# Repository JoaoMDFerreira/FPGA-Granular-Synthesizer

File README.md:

# FPGA Implementation of a Real-time Synthetic-Based Granular Synthesizer
This repo contains the source code backup of the thesis. The topic of the thesis is "FPGA Implementation of a Real-time Synthetic-Based Granular Synthesizer".
A diagram of the implementation is shown below.

The final binary is given as BOOT.bin.

## VHDL Source Files
The VHDL project was not backed up, only its source files. These files are available in the vhdl_src folder.

## PCB Files
The KiCad files for a breakout board developed for the Z-turn board V2 are given in the Breakout folder.

## MATLAB Source Files
MATLAB source files are given in the matlab_src.

## Extras
Some extra files are contained in the misc_src folder. Some of these are scripts used to generate plots for the thesis, there are some exploratory scripts towards pitch_shifting that was future work for the thesis and finally there is a C script used to generate code for the MIDI_LUT.

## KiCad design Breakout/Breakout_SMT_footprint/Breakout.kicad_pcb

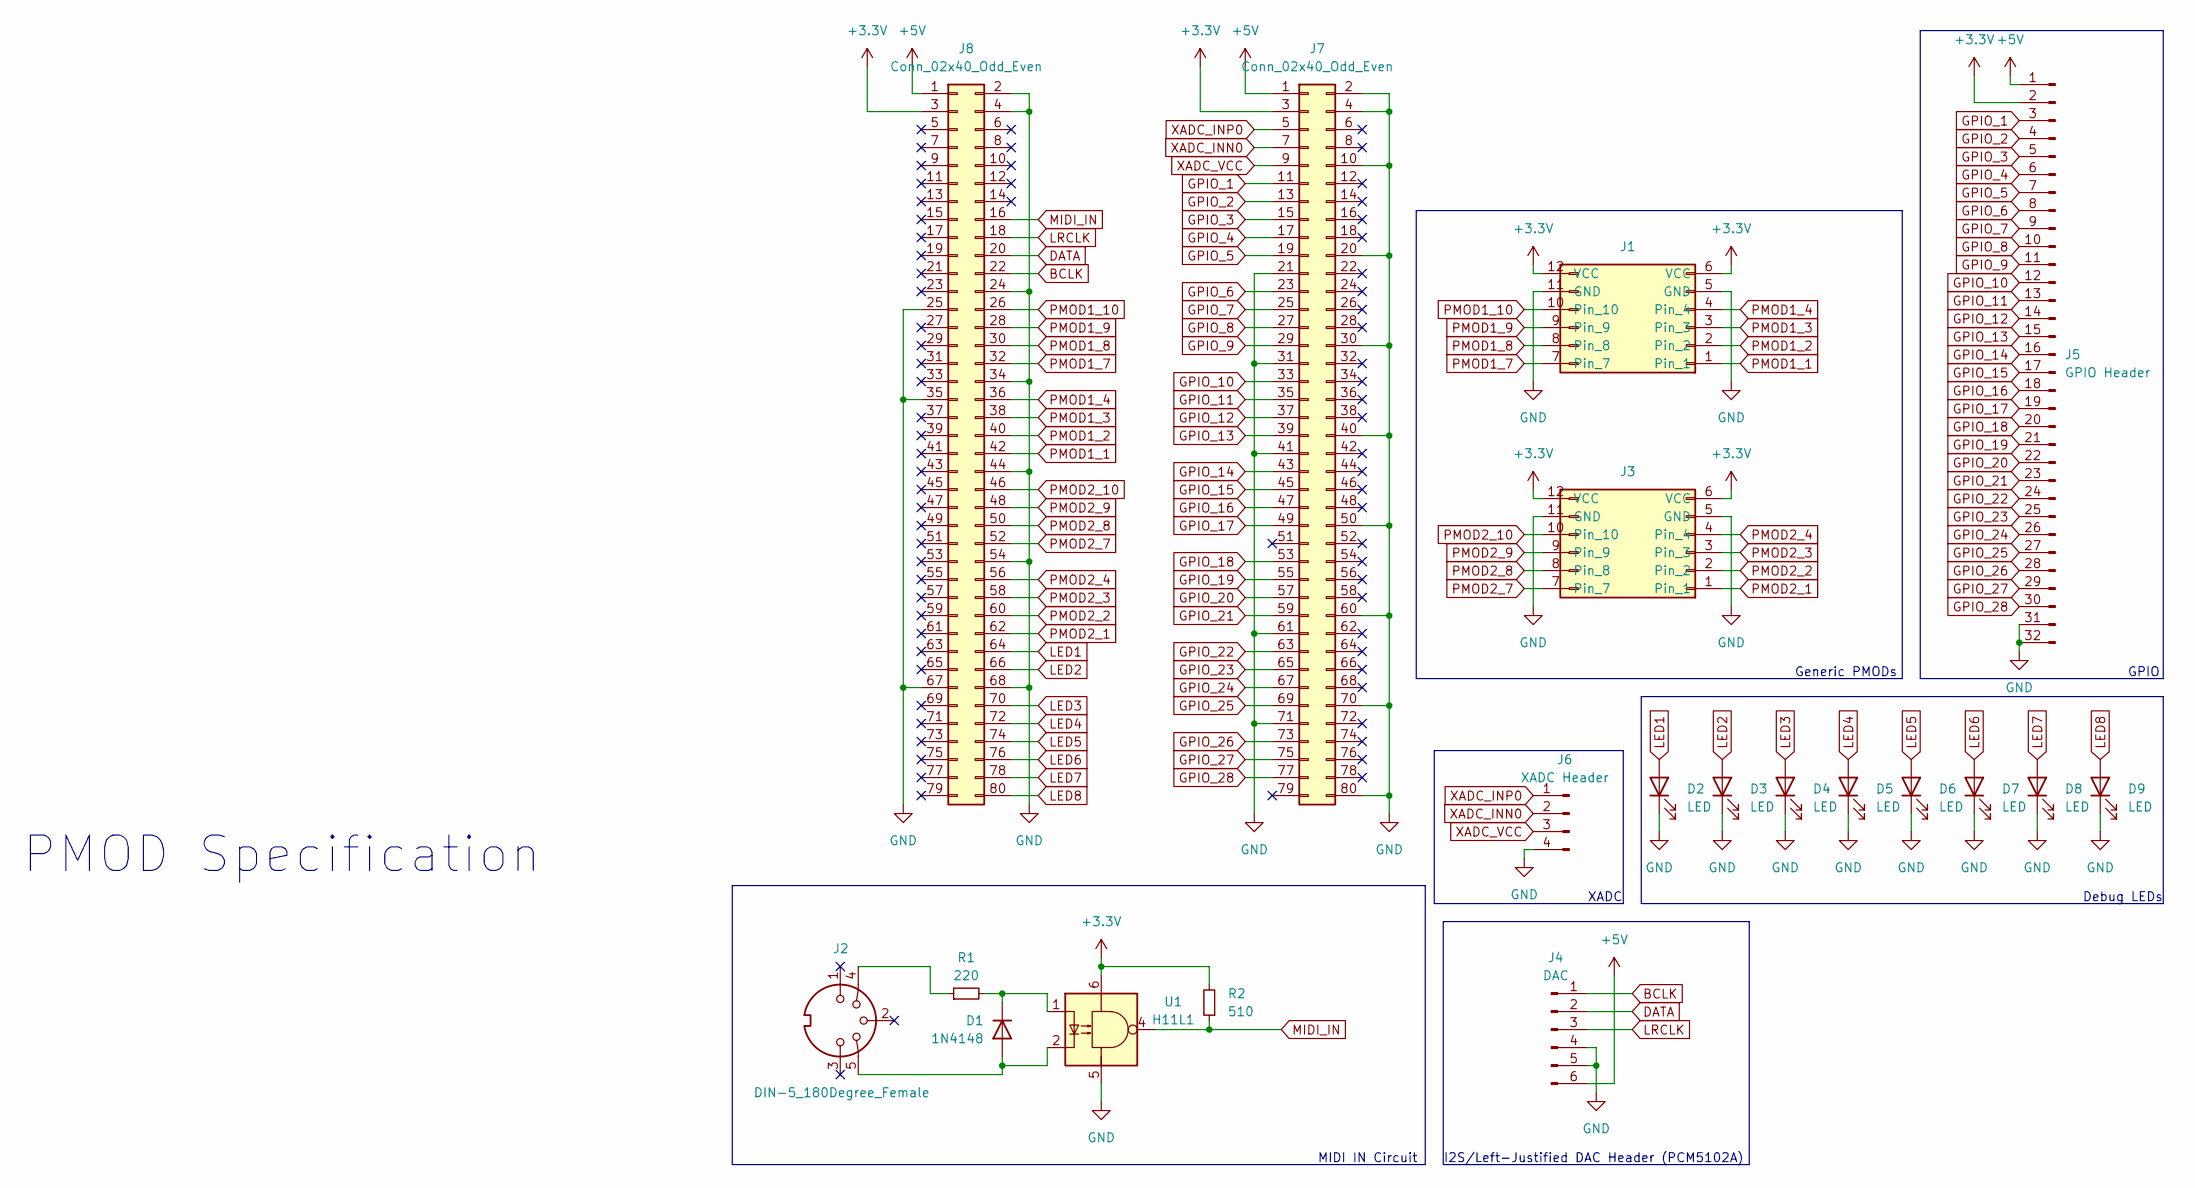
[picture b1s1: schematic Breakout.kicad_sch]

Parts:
D1: 1N4148; D_DO-35_SOD27_P7.62mm_Horizontal; LCSC C402212
D2, D3, D4, D5, D6, D7, D8, D9: LED; LED_D3.0mm; LCSC C7433021
J1, J3: PMOD; LCSC C5383091
J2: DIN-5_180Degree_Female; MIDI_DIN5; LCSC C2939346
J4: DAC; PinHeader_1x06_P2.54mm_Horizontal; LCSC C19190480
J5: GPIO Header; PinHeader_1x32_P2.54mm_Vertical; LCSC C7430388
J6: XADC Header; PinSocket_1x04_P2.54mm_Vertical; LCSC C2935929
J7, J8: Conn_02x40_Odd_Even; 2x40 Inverted; LCSC C545212
R1: 220; R_Axial_DIN0204_L3.6mm_D1.6mm_P5.08mm_Horizontal; LCSC C1367947
R2: 510; R_Axial_DIN0204_L3.6mm_D1.6mm_P5.08mm_Horizontal; LCSC C1396546
U1: H11L1; DIP-6_W7.62mm_Socket_LongPads; LCSC C78588

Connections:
+3.3V: J1.6 (VCC), J1.12 (VCC), J3.6 (VCC), J3.12 (VCC), J5.2, J7.3, J8.3, R2.2, U1.6
+5V: J4.6, J5.1, J7.1, J8.1
BCLK: J4.1, J8.22
DATA: J4.2, J8.20
GND: D2.1 (K), D3.1 (K), D4.1 (K), D5.1 (K), D6.1 (K), D7.1 (K), D8.1 (K), D9.1 (K), J1.5 (GND), J1.11 (GND), J3.5 (GND), J3.11 (GND), J4.4, J4.5, J5.31, J5.32, J6.4, J7.2, J7.4, J7.10, J7.20, J7.21, J7.30, J7.31, J7.40, J7.41, J7.50, J7.60, J7.61, J7.70, J7.71, J7.80, J8.2, J8.4, J8.24, J8.25, J8.34, J8.35, J8.44, J8.54, J8.67, J8.68, U1.5
GPIO_1: J5.3, J7.11
GPIO_2: J5.4, J7.13
GPIO_3: J5.5, J7.15
GPIO_4: J5.6, J7.17
GPIO_5: J5.7, J7.19
GPIO_6: J5.8, J7.23
GPIO_7: J5.9, J7.25
GPIO_8: J5.10, J7.27
GPIO_9: J5.11, J7.29
GPIO_10: J5.12, J7.33
GPIO_11: J5.13, J7.35
GPIO_12: J5.14, J7.37
GPIO_13: J5.15, J7.39
GPIO_14: J5.16, J7.43
GPIO_15: J5.17, J7.45
GPIO_16: J5.18, J7.47
GPIO_17: J5.19, J7.49
GPIO_18: J5.20, J7.53
GPIO_19: J5.21, J7.55
GPIO_20: J5.22, J7.57
GPIO_21: J5.23, J7.59
GPIO_22: J5.24, J7.63
GPIO_23: J5.25, J7.65
GPIO_24: J5.26, J7.67
GPIO_25: J5.27, J7.69
GPIO_26: J5.28, J7.73
GPIO_27: J5.29, J7.75
GPIO_28: J5.30, J7.77
LED1: D2.2 (A), J8.64
LED2: D3.2 (A), J8.66
LED3: D4.2 (A), J8.70
LED4: D5.2 (A), J8.72
LED5: D6.2 (A), J8.74
LED6: D7.2 (A), J8.76
LED7: D8.2 (A), J8.78
LED8: D9.2 (A), J8.80
LRCLK: J4.3, J8.18
MIDI_IN: J8.16, R2.1, U1.4
unnamed: D1.2 (A), J2.5, U1.2
unnamed: D1.1 (K), R1.2, U1.1
unnamed: J2.4, R1.1
PMOD1_1: J1.1, J8.42
PMOD1_2: J1.2, J8.40
PMOD1_3: J1.3, J8.38
PMOD1_4: J1.4, J8.36
PMOD1_7: J1.7, J8.32
PMOD1_8: J1.8, J8.30
PMOD1_9: J1.9, J8.28
PMOD1_10: J1.10, J8.26
PMOD2_1: J3.1, J8.62
PMOD2_2: J3.2, J8.60
PMOD2_3: J3.3, J8.58
PMOD2_4: J3.4, J8.56
PMOD2_7: J3.7, J8.52
PMOD2_8: J3.8, J8.50
PMOD2_9: J3.9, J8.48
PMOD2_10: J3.10, J8.46
XADC_INN0: J6.2, J7.7
XADC_INP0: J6.1, J7.5
XADC_VCC: J6.3, J7.9

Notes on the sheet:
PMOD Specification
I2S/Left-Justified DAC Header (PCM5102A)
GPIO
Generic PMODs
Debug LEDs
MIDI IN Circuit
XADC

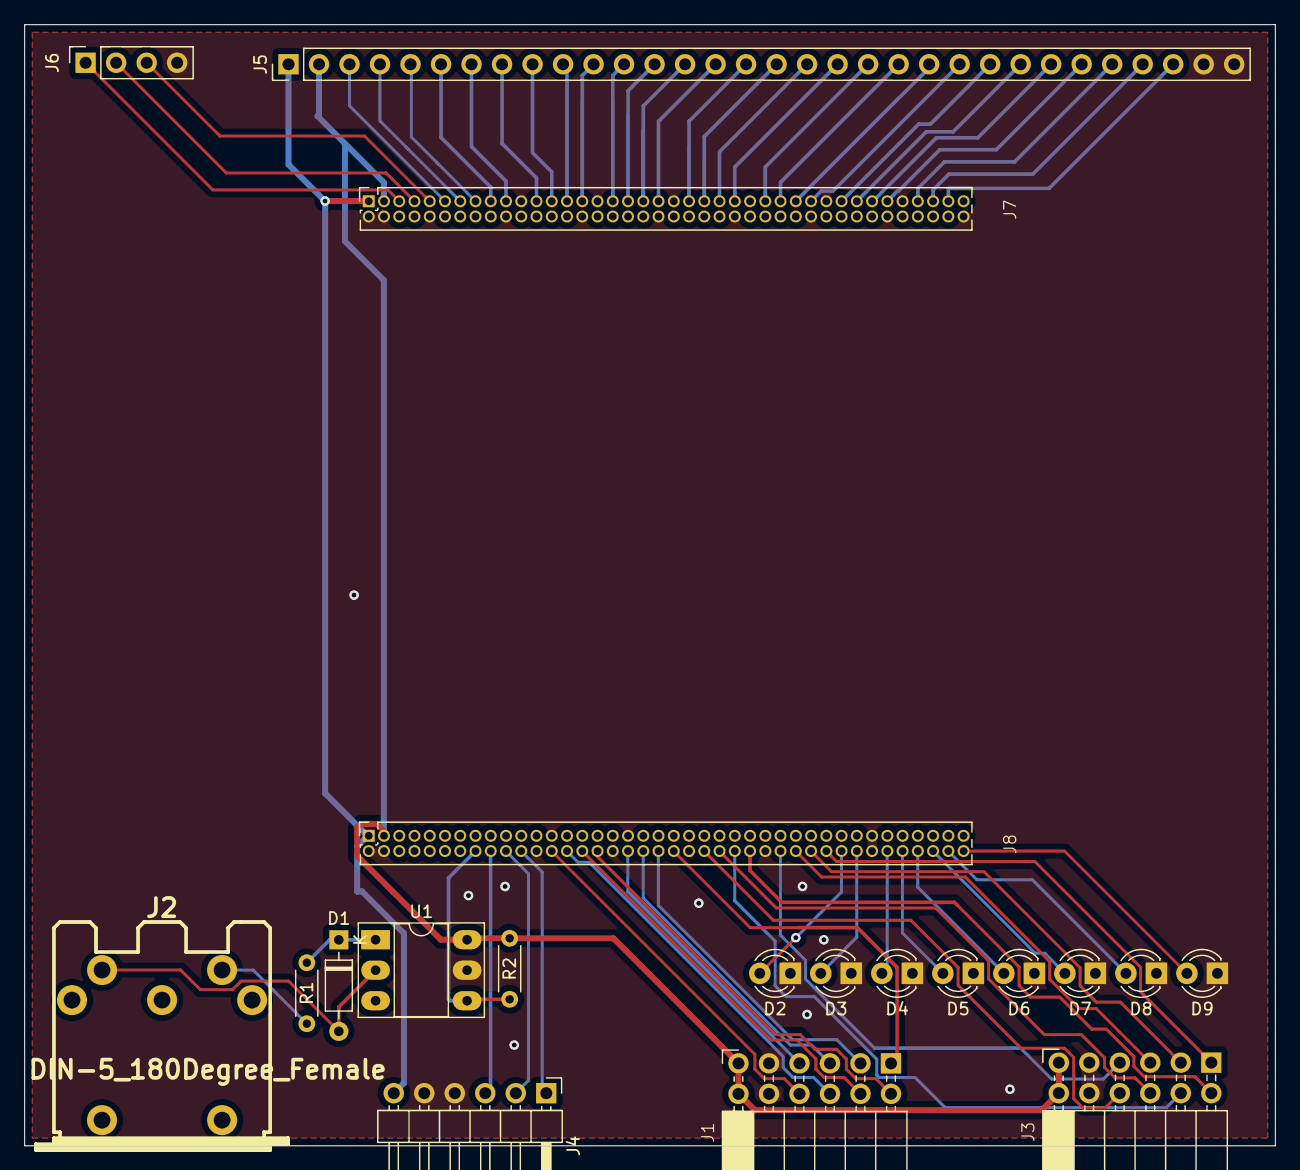
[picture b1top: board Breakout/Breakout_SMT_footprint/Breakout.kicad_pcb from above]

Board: 2 copper layers, 104.1 x 93.3 mm, 20 parts (0 on the bottom side), 65 nets.

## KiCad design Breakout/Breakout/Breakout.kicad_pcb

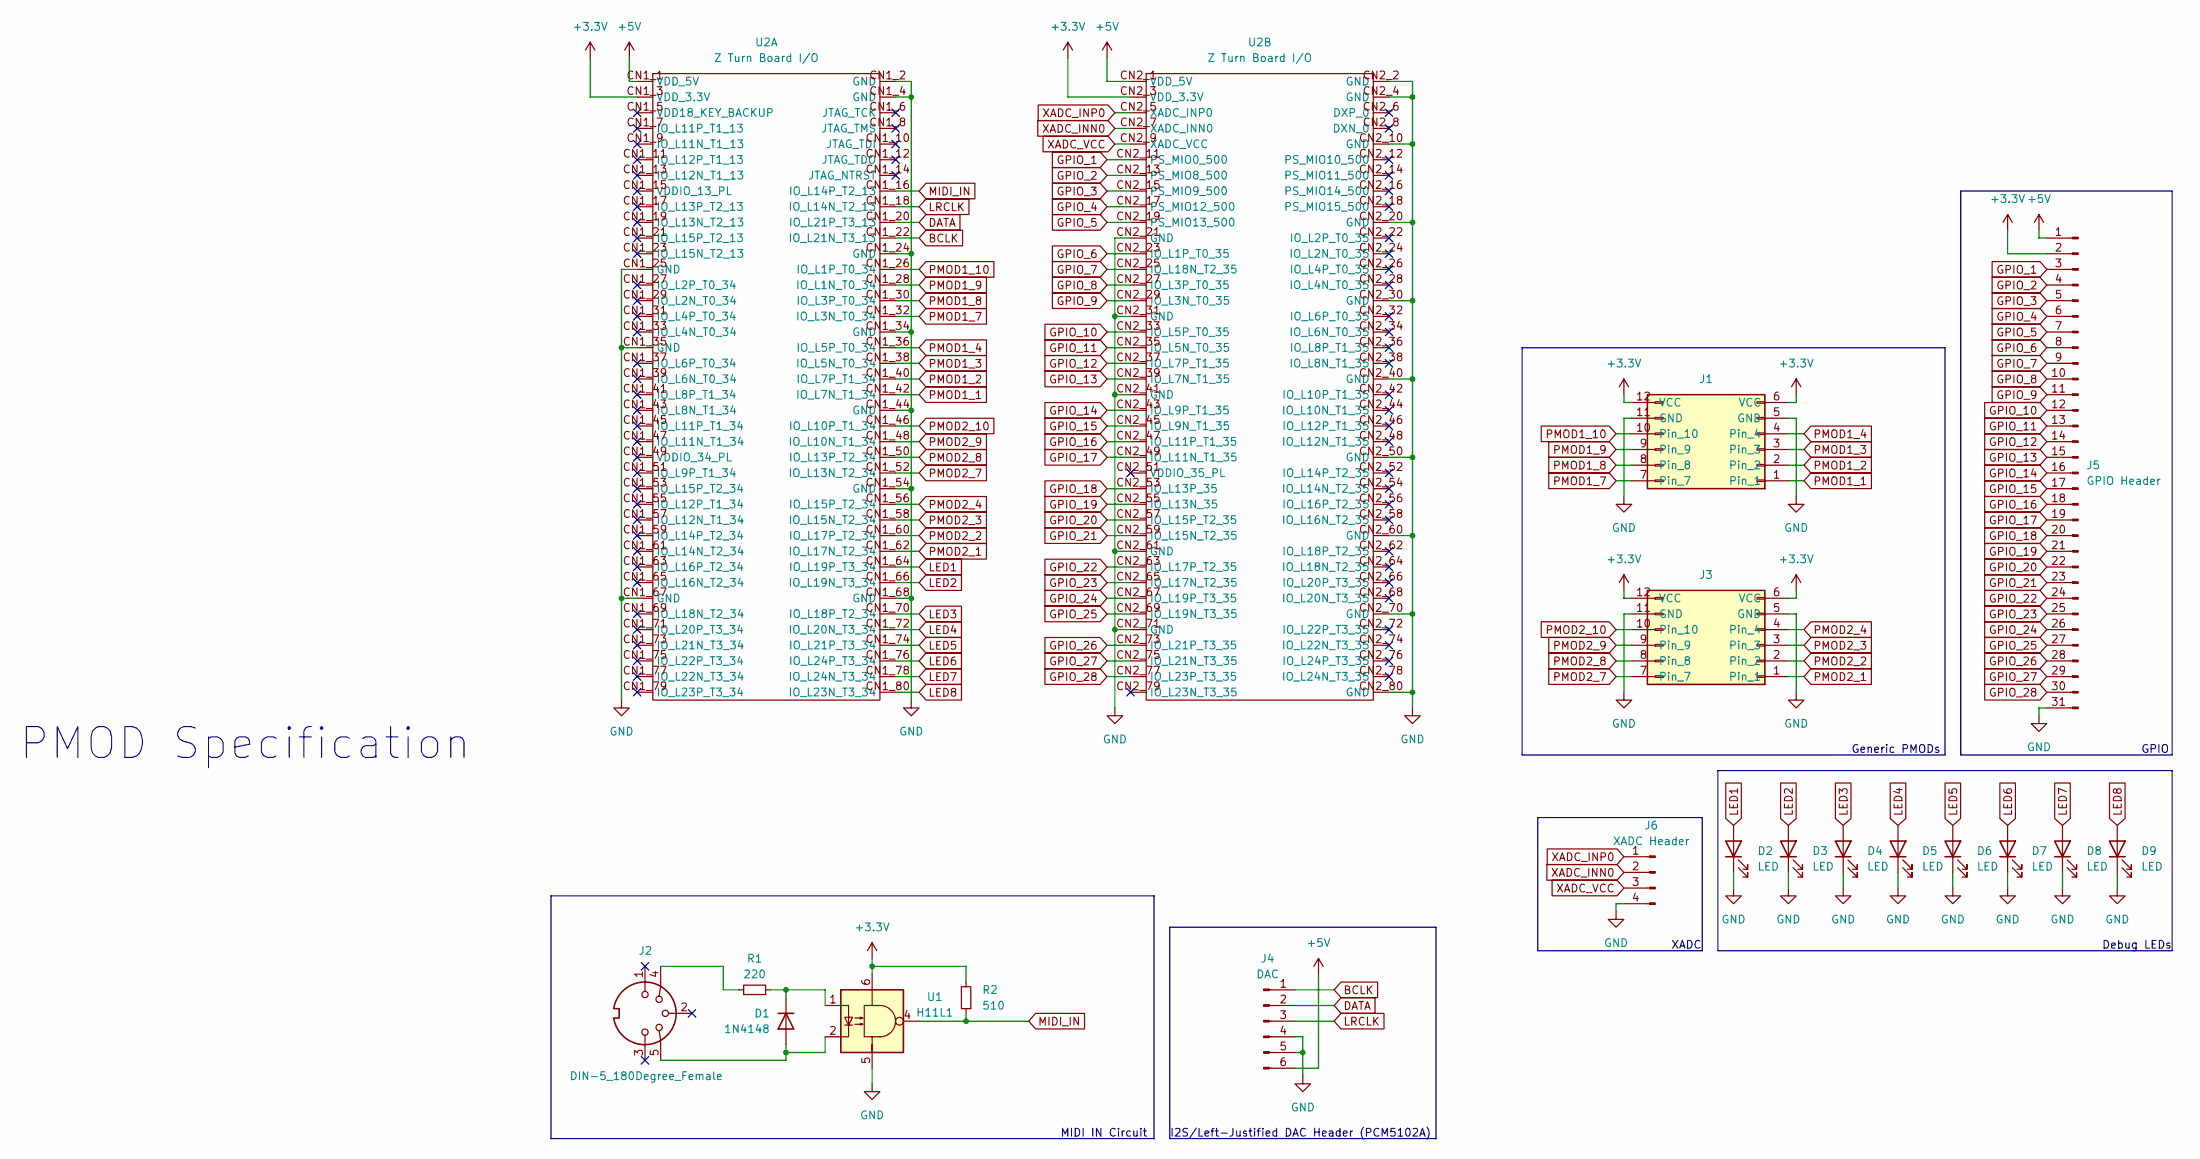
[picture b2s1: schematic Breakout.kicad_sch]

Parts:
D1: 1N4148; D_DO-35_SOD27_P7.62mm_Horizontal; LCSC C402212
D2, D3, D4, D5, D6, D7, D8, D9: LED; LED_D3.0mm; LCSC C7433021
J1, J3: PMOD; LCSC C5383091
J2: DIN-5_180Degree_Female; MIDI_DIN5; LCSC C2939346
J4: DAC; PinHeader_1x06_P2.54mm_Horizontal; LCSC C19190480
J5: GPIO Header; PinSocket_1x31_P2.54mm_Vertical; LCSC C2883719
J6: XADC Header; PinSocket_1x04_P2.54mm_Vertical; LCSC C18164982
R1: 220; R_Axial_DIN0204_L3.6mm_D1.6mm_P5.08mm_Horizontal; LCSC C1367947
R2: 510; R_Axial_DIN0204_L3.6mm_D1.6mm_P5.08mm_Horizontal; LCSC C1396546
U1: H11L1; DIP-6_W7.62mm_Socket_LongPads; LCSC C78588
U2: Z Turn Board I/O; Z Turn Board IO; LCSC C545212

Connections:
+3.3V: J1.6 (VCC), J1.12 (VCC), J3.6 (VCC), J3.12 (VCC), J5.2, R2.2, U1.6, U2.CN1_3 (VDD_3.3V), U2.CN2_3 (VDD_3.3V)
+5V: J4.6, J5.1, U2.CN1_1 (VDD_5V), U2.CN2_1 (VDD_5V)
BCLK: J4.1, U2.CN1_22 (IO_L21N_T3_13)
DATA: J4.2, U2.CN1_20 (IO_L21P_T3_13)
GND: D2.1 (K), D3.1 (K), D4.1 (K), D5.1 (K), D6.1 (K), D7.1 (K), D8.1 (K), D9.1 (K), J1.5 (GND), J1.11 (GND), J3.5 (GND), J3.11 (GND), J4.4, J4.5, J5.31, J6.4, U1.5, U2.CN1_2 (GND), U2.CN1_4 (GND), U2.CN1_24 (GND), U2.CN1_25 (GND), U2.CN1_34 (GND), U2.CN1_35 (GND), U2.CN1_44 (GND), U2.CN1_54 (GND), U2.CN1_67 (GND), U2.CN1_68 (GND), U2.CN2_2 (GND), U2.CN2_4 (GND), U2.CN2_10 (GND), U2.CN2_20 (GND), U2.CN2_21 (GND), U2.CN2_30 (GND), U2.CN2_31 (GND), U2.CN2_40 (GND), U2.CN2_41 (GND), U2.CN2_50 (GND), U2.CN2_60 (GND), U2.CN2_61 (GND), U2.CN2_70 (GND), U2.CN2_71 (GND), U2.CN2_80 (GND)
GPIO_1: J5.3, U2.CN2_11 (PS_MIO0_500)
GPIO_2: J5.4, U2.CN2_13 (PS_MIO8_500)
GPIO_3: J5.5, U2.CN2_15 (PS_MIO9_500)
GPIO_4: J5.6, U2.CN2_17 (PS_MIO12_500)
GPIO_5: J5.7, U2.CN2_19 (PS_MIO13_500)
GPIO_6: J5.8, U2.CN2_23 (IO_L1P_T0_35)
GPIO_7: J5.9, U2.CN2_25 (IO_L18N_T2_35)
GPIO_8: J5.10, U2.CN2_27 (IO_L3P_T0_35)
GPIO_9: J5.11, U2.CN2_29 (IO_L3N_T0_35)
GPIO_10: J5.12, U2.CN2_33 (IO_L5P_T0_35)
GPIO_11: J5.13, U2.CN2_35 (IO_L5N_T0_35)
GPIO_12: J5.14, U2.CN2_37 (IO_L7P_T1_35)
GPIO_13: J5.15, U2.CN2_39 (IO_L7N_T1_35)
GPIO_14: J5.16, U2.CN2_43 (IO_L9P_T1_35)
GPIO_15: J5.17, U2.CN2_45 (IO_L9N_T1_35)
GPIO_16: J5.18, U2.CN2_47 (IO_L11P_T1_35)
GPIO_17: J5.19, U2.CN2_49 (IO_L11N_T1_35)
GPIO_18: J5.20, U2.CN2_53 (IO_L13P_35)
GPIO_19: J5.21, U2.CN2_55 (IO_L13N_35)
GPIO_20: J5.22, U2.CN2_57 (IO_L15P_T2_35)
GPIO_21: J5.23, U2.CN2_59 (IO_L15N_T2_35)
GPIO_22: J5.24, U2.CN2_63 (IO_L17P_T2_35)
GPIO_23: J5.25, U2.CN2_65 (IO_L17N_T2_35)
GPIO_24: J5.26, U2.CN2_67 (IO_L19P_T3_35)
GPIO_25: J5.27, U2.CN2_69 (IO_L19N_T3_35)
GPIO_26: J5.28, U2.CN2_73 (IO_L21P_T3_35)
GPIO_27: J5.29, U2.CN2_75 (IO_L21N_T3_35)
GPIO_28: J5.30, U2.CN2_77 (IO_L23P_T3_35)
LED1: D2.2 (A), U2.CN1_64 (IO_L19P_T3_34)
LED2: D3.2 (A), U2.CN1_66 (IO_L19N_T3_34)
LED3: D4.2 (A), U2.CN1_70 (IO_L18P_T2_34)
LED4: D5.2 (A), U2.CN1_72 (IO_L20N_T3_34)
LED5: D6.2 (A), U2.CN1_74 (IO_L21P_T3_34)
LED6: D7.2 (A), U2.CN1_76 (IO_L24P_T3_34)
LED7: D8.2 (A), U2.CN1_78 (IO_L24N_T3_34)
LED8: D9.2 (A), U2.CN1_80 (IO_L23N_T3_34)
LRCLK: J4.3, U2.CN1_18 (IO_L14N_T2_13)
MIDI_IN: R2.1, U1.4, U2.CN1_16 (IO_L14P_T2_13)
unnamed: D1.2 (A), J2.5, U1.2
unnamed: D1.1 (K), R1.2, U1.1
unnamed: J2.4, R1.1
PMOD1_1: J1.1, U2.CN1_42 (IO_L7N_T1_34)
PMOD1_2: J1.2, U2.CN1_40 (IO_L7P_T1_34)
PMOD1_3: J1.3, U2.CN1_38 (IO_L5N_T0_34)
PMOD1_4: J1.4, U2.CN1_36 (IO_L5P_T0_34)
PMOD1_7: J1.7, U2.CN1_32 (IO_L3N_T0_34)
PMOD1_8: J1.8, U2.CN1_30 (IO_L3P_T0_34)
PMOD1_9: J1.9, U2.CN1_28 (IO_L1N_T0_34)
PMOD1_10: J1.10, U2.CN1_26 (IO_L1P_T0_34)
PMOD2_1: J3.1, U2.CN1_62 (IO_L17N_T2_34)
PMOD2_2: J3.2, U2.CN1_60 (IO_L17P_T2_34)
PMOD2_3: J3.3, U2.CN1_58 (IO_L15N_T2_34)
PMOD2_4: J3.4, U2.CN1_56 (IO_L15P_T2_34)
PMOD2_7: J3.7, U2.CN1_52 (IO_L13N_T2_34)
PMOD2_8: J3.8, U2.CN1_50 (IO_L13P_T2_34)
PMOD2_9: J3.9, U2.CN1_48 (IO_L10N_T1_34)
PMOD2_10: J3.10, U2.CN1_46 (IO_L10P_T1_34)
XADC_INN0: J6.2, U2.CN2_7 (XADC_INN0)
XADC_INP0: J6.1, U2.CN2_5 (XADC_INP0)
XADC_VCC: J6.3, U2.CN2_9 (XADC_VCC)

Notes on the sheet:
PMOD Specification
I2S/Left-Justified DAC Header (PCM5102A)
GPIO
Generic PMODs
Debug LEDs
MIDI IN Circuit
XADC

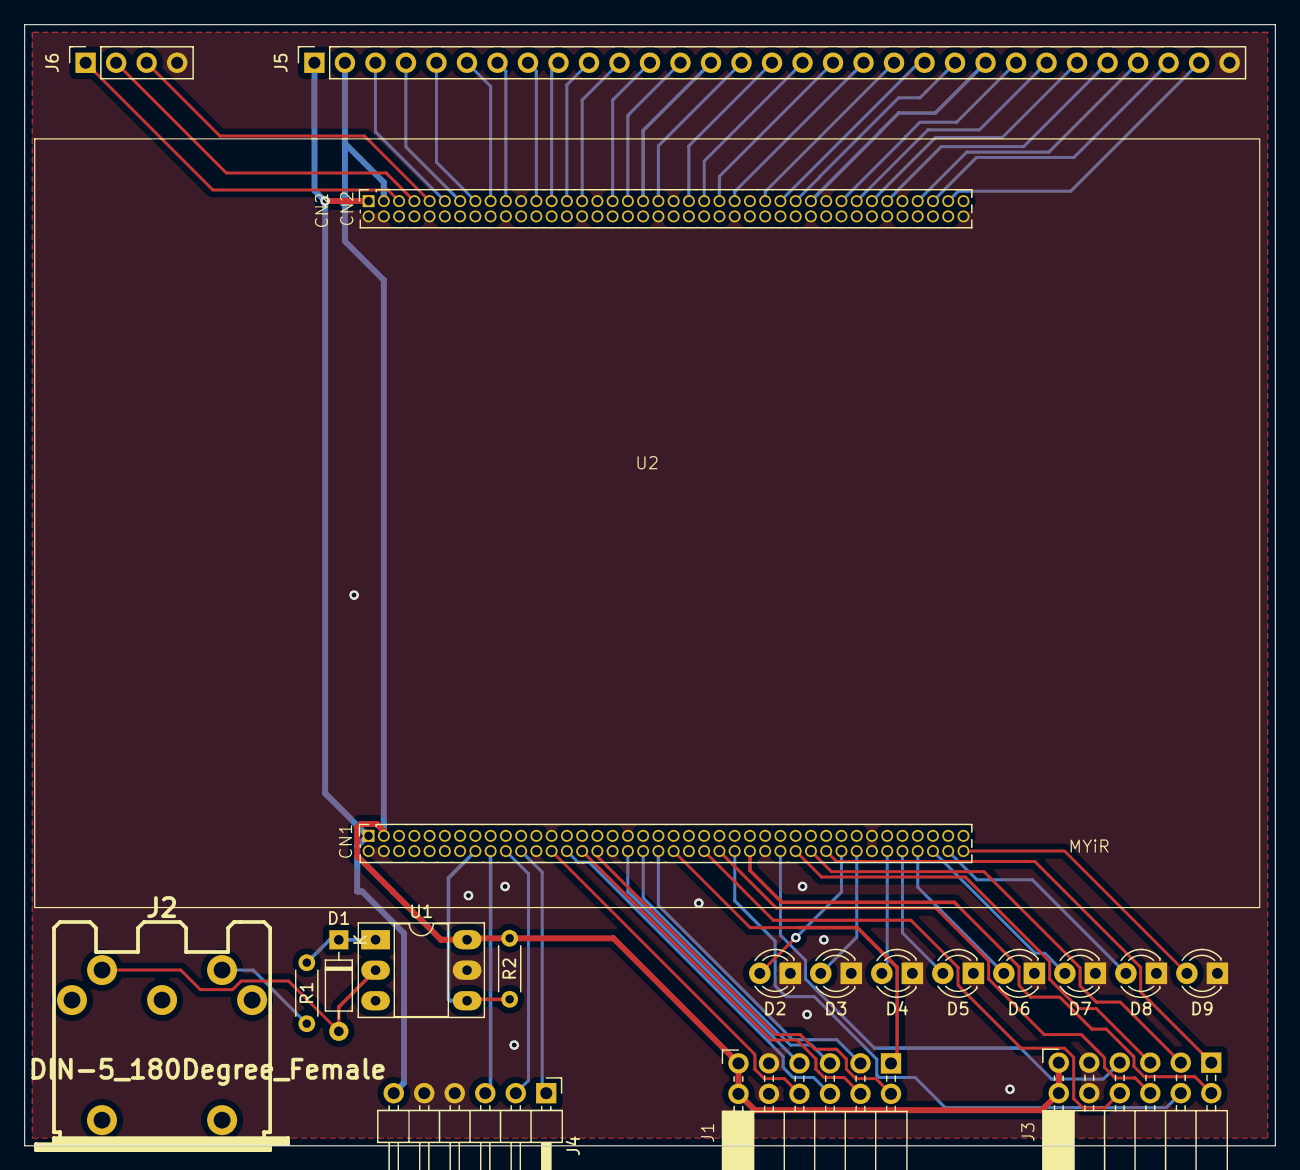
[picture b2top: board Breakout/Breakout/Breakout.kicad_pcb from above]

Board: 2 copper layers, 104.1 x 93.3 mm, 19 parts (0 on the bottom side), 65 nets.
